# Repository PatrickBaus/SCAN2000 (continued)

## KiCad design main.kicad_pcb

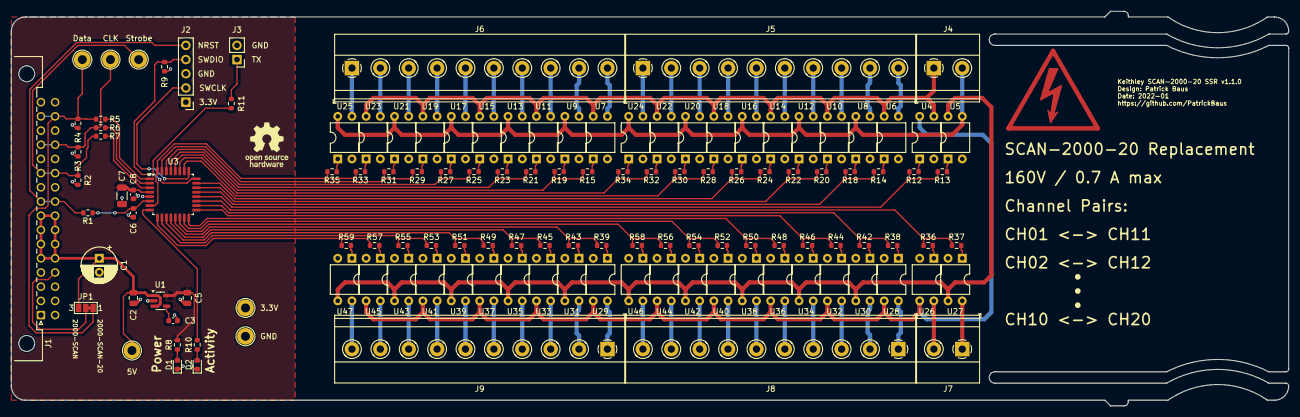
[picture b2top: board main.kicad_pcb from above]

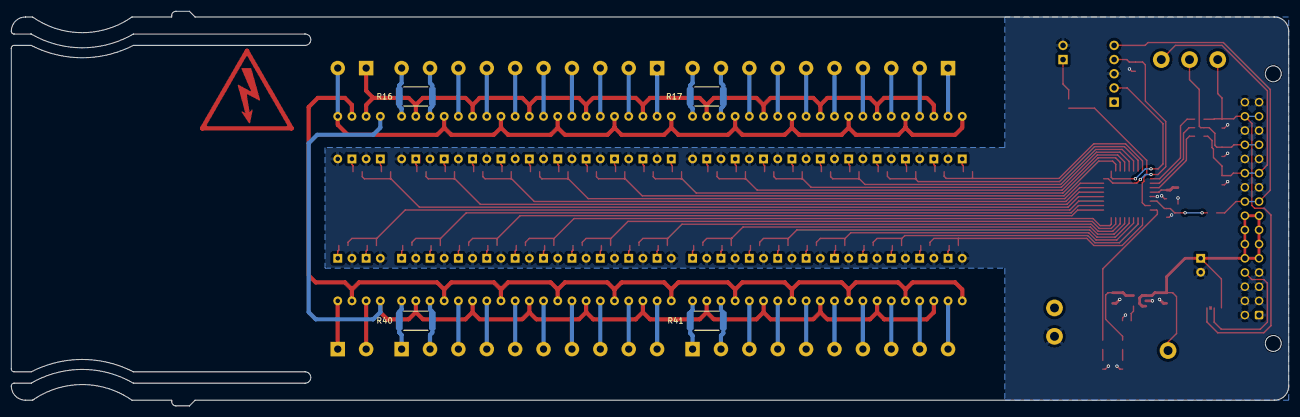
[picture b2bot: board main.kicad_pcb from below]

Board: 2 copper layers, 228.6 x 70.6 mm, 132 parts (4 on the bottom side), 132 nets.

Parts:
C1: 10u; CP_Radial_D6.3mm_P2.50mm
C2, C5: 1u; C_0805_2012Metric
C3, C6, C8: 100n; C_0603_1608Metric
C7: 4.7u; C_1206_3216Metric
D1, D2: Green; LED_0603_1608Metric
J1: Conn_02x16_Row_Letter_First; DIN41612_B2_2x16_Male_Horizontal_THT
J2: Conn_01x05; PinHeader_1x05_P2.54mm_Vertical
J3: Conn_01x02; PinHeader_1x02_P2.54mm_Vertical
J4, J7: Screw_Terminal_01x02; TerminalBlock_Phoenix_SMKDSN-1,5-2-5.08_1x02_P5.08mm_Horizo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
J5, J6, J8, J9: Screw_Terminal_01x10; TerminalBlock_Phoenix_SMKDSN-1,5-10-5.08_1x10_P5.08mm_Horiz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
JP1: SolderJumper_3_Bridged12; SolderJumper-3_P1.3mm_Bridged12_Pad1.0x1.5mm_NumberLabels
LOGO2: Logo_Open_Hardware_Small; OSHW-Logo_7.5x8mm_SilkScreen
R1, R5, R6, R7, R8, R10, R11, R12, R13, R14, R15, R18, R19, R20, R21, R22, R23, R24, R25, R26, R27, R28, R29, R30, R31, R32, R33, R34, R35, R36, R37, R38, R39, R42, R43, R44, R45, R46, R47, R48, R49, R50, R51, R52, R53, R54, R55, R56, R57, R58, R59: 330R; R_0603_1608Metric
R2, R3, R4, R9: 10k; R_0603_1608Metric
R16, R17, R40, R41: 2m; R_2512_6332Metric
SYM1: SYM_Flash_Small; Symbol_HighVoltage_Triangle_17x15mm_Copper
TP1, TP2, TP3, TP4, TP5, TP6: TestPoint; TestPoint_Loop_D2.60mm_Drill1.6mm_Beaded
U1: TPS73233DBVR; SOT-23-5
U3: STM32G070KBT6; LQFP-32_7x7mm_P0.8mm
U4, U5, U6, U7, U8, U9, U10, U11, U12, U13, U14, U15, U16, U17, U18, U19, U20, U21, U22, U23, U24, U25, U26, U27, U28, U29, U30, U31, U32, U33, U34, U35, U36, U37, U38, U39, U40, U41, U42, U43, U44, U45, U46, U47: TLP3558A; DIP-4_W7.62mm

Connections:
+3V3: C5.1, C7.1, C8.1, J2.1, R8.1, TP2.1, U1.5 (OUT), U3.4 (VDD/VDDA)
+5V: C1.1, C2.1, J1.a5, J1.a6, J1.a7, J1.a8, J1.b5, J1.b6, J1.b7, J1.b8, JP1.3 (B), TP1.1, U1.1 (IN), U1.3 (EN)
/CLK: J1.a13, J1.b13, R3.1, R6.2, TP5.1
/DATA: J1.a15, J1.b15, JP1.1 (A), R4.1, R5.2, TP4.1
/ID: J1.b4, JP1.2 (C)
/Microcontroller/Bus2_input_enable: R12.2, R13.2, U3.20 (PC6)
/Microcontroller/Bus2_sense_enable: R36.2, R37.2, U3.19 (PA9)
/Microcontroller/CH1: R14.2, R18.2, U3.21 (PA10)
/Microcontroller/CH2: R20.2, R22.2, U3.22 (PA11)
/Microcontroller/CH3: R24.2, R26.2, U3.23 (PA12)
/Microcontroller/CH4: R28.2, R30.2, U3.26 (PA15)
/Microcontroller/CH5: R32.2, R34.2, U3.27 (PB3)
/Microcontroller/CH6: R15.2, R19.2, U3.28 (PB4)
/Microcontroller/CH7: R21.2, R23.2, U3.29 (PB5)
/Microcontroller/CH8: R25.2, R27.2, U3.30 (PB6)
/Microcontroller/CH9: R29.2, R31.2, U3.31 (PB7)
/Microcontroller/CH10: R33.2, R35.2, U3.32 (PB8)
/Microcontroller/CH11: R38.2, R42.2, U3.18 (PA8)
/Microcontroller/CH12: R44.2, R46.2, U3.17 (PB2)
/Microcontroller/CH13: R48.2, R50.2, U3.16 (PB1)
/Microcontroller/CH14: R52.2, R54.2, U3.15 (PB0)
/Microcontroller/CH15: R56.2, R58.2, U3.14 (PA7)
/Microcontroller/CH16: R39.2, R43.2, U3.13 (PA6)
/Microcontroller/CH17: R45.2, R47.2, U3.12 (PA5)
/Microcontroller/CH18: R49.2, R51.2, U3.11 (PA4)
/Microcontroller/CH19: R53.2, R55.2, U3.10 (PA3)
/Microcontroller/CH20: R57.2, R59.2, U3.9 (PA2)
/Microcontroller/CLK: R6.1, U3.2 (PC14)
/Microcontroller/DATA: R5.1, U3.1 (PB9)
/Microcontroller/LED: R10.1, U3.8 (PA1)
/Microcontroller/STROBE: R7.1, U3.3 (PC15)
/Microcontroller/SWCLK: J2.2, U3.25 (PA14)
/Microcontroller/SWDIO: J2.4, R9.1, U3.24 (PA13)
/Microcontroller/TX: R11.2, U3.7 (PA0)
/Relays/Input pins/Bus_HIGH: U4.4, U26.3, U28.3, U29.3, U32.3, U33.3, U36.3, U37.3, U40.3, U41.3, U44.3, U45.3
/Relays/Input pins/Bus_LOW: U5.4, U27.3, U30.3, U31.3, U34.3, U35.3, U38.3, U39.3, U42.3, U43.3, U46.3, U47.3
/Relays/Input pins/Out_HIGH: J4.1, U4.3, U6.4, U7.4, U10.4, U11.4, U14.4, U15.4, U18.4, U19.4, U22.4, U23.4
/Relays/Input pins/Out_LOW: J4.2, U5.3, U8.4, U9.4, U12.4, U13.4, U16.4, U17.4, U20.4, U21.4, U24.4, U25.4
/Relays/Input/Sense pins/Sense_HIGH: J7.2, U26.4
/Relays/Input/Sense pins/Sense_LOW: J7.1, U27.4
/STROBE: J1.a11, J1.b11, R2.1, R7.2, TP6.1
/~NRST: J1.a9, J1.b9, J2.5, R1.2
GND: C1.2, C2.2, C3.2, C5.2, C6.2, C7.2, C8.2, D1.1 (K), D2.1 (K), J1.a1, J1.a2, J1.a3, J1.a4, J1.a10, J1.a12, J1.a14, J1.a16, J1.b1, J1.b2, J1.b3, J1.b10, J1.b12, J1.b14, J1.b16, J2.3, J3.2, R2.2, R3.2, R4.2, R9.2, TP3.1, U1.2 (GND), U3.5 (VSS/VSSA), U4.2, U5.2, U6.2, U7.2, U8.2, U9.2, U10.2, U11.2, U12.2, U13.2, U14.2, U15.2, U16.2, U17.2, U18.2, U19.2, U20.2, U21.2, U22.2, U23.2, U24.2, U25.2, U26.2, U27.2, U28.2, U29.2, U30.2, U31.2, U32.2, U33.2, U34.2, U35.2, U36.2, U37.2, U38.2, U39.2, U40.2, U41.2, U42.2, U43.2, U44.2, U45.2, U46.2, U47.2
unnamed: D1.2 (A), R8.2
unnamed: D2.2 (A), R10.2
unnamed: J3.1, R11.1
unnamed: J5.1, U24.3
unnamed: J5.2, U22.3
unnamed: J5.3, U20.3
unnamed: J5.4, U18.3
unnamed: J5.5, U16.3
unnamed: J5.6, U14.3
unnamed: J5.7, U12.3
unnamed: J5.8, U10.3
unnamed: J5.9, R16.1, U8.3
unnamed: J5.10, R16.2, U6.3
unnamed: J6.1, U25.3
unnamed: J6.2, U23.3
unnamed: J6.3, U21.3
unnamed: J6.4, U19.3
unnamed: J6.5, U17.3
unnamed: J6.6, U15.3
unnamed: J6.7, U13.3
unnamed: J6.8, U11.3
unnamed: J6.9, R17.1, U9.3
unnamed: J6.10, R17.2, U7.3
unnamed: J8.1, R40.2, U28.4
unnamed: J8.2, R40.1, U30.4
unnamed: J8.3, U32.4
unnamed: J8.4, U34.4
unnamed: J8.5, U36.4
unnamed: J8.6, U38.4
unnamed: J8.7, U40.4
unnamed: J8.8, U42.4
unnamed: J8.9, U44.4
unnamed: J8.10, U46.4
unnamed: J9.1, R41.2, U29.4
unnamed: J9.2, R41.1, U31.4
unnamed: J9.3, U33.4
unnamed: J9.4, U35.4
unnamed: J9.5, U37.4
unnamed: J9.6, U39.4
unnamed: J9.7, U41.4
unnamed: J9.8, U43.4
unnamed: J9.9, U45.4
unnamed: J9.10, U47.4
unnamed: R12.1, U4.1
unnamed: R13.1, U5.1
unnamed: R14.1, U6.1
unnamed: R15.1, U7.1
unnamed: R18.1, U8.1
unnamed: R19.1, U9.1
unnamed: R20.1, U10.1
unnamed: R21.1, U11.1
unnamed: R22.1, U12.1
unnamed: R23.1, U13.1
unnamed: R24.1, U14.1
unnamed: R25.1, U15.1
unnamed: R26.1, U16.1
unnamed: R27.1, U17.1
unnamed: R28.1, U18.1
unnamed: R29.1, U19.1
unnamed: R30.1, U20.1
unnamed: R31.1, U21.1
unnamed: R32.1, U22.1
unnamed: R33.1, U23.1
unnamed: R34.1, U24.1
unnamed: R35.1, U25.1
unnamed: R36.1, U26.1
unnamed: R37.1, U27.1
unnamed: R38.1, U28.1
unnamed: R39.1, U29.1
unnamed: R42.1, U30.1
unnamed: R43.1, U31.1
unnamed: R44.1, U32.1
unnamed: R45.1, U33.1
unnamed: R46.1, U34.1
unnamed: R47.1, U35.1
unnamed: R48.1, U36.1
unnamed: R49.1, U37.1
unnamed: R50.1, U38.1
unnamed: R51.1, U39.1
unnamed: R52.1, U40.1
unnamed: R53.1, U41.1
unnamed: R54.1, U42.1
unnamed: R55.1, U43.1
unnamed: R56.1, U44.1
unnamed: R57.1, U45.1
unnamed: R58.1, U46.1
unnamed: R59.1, U47.1
unnamed: C3.1, U1.4 (NR)
unnamed: C6.1, R1.1, U3.6 (NRST)

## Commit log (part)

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2022-01-11 Added link to the firmware
2022-01-11 Replaced Picoblade connector with standard pin header Updated libraries to KiCAD 6 format
2022-01-11 Updated PCB picture to latest version
2022-01-11 Added description to the photo
2022-01-11 Add a note, that v1.1.0 and above have a rotated MCU
2022-01-15 Updated documentation
2022-01-17 Updated silkscreen
2022-01-17 Updated BOM
2022-01-18 Updated readme with more details about supported DMMs.
2022-01-31 Added screenshots of the serial data
2022-02-20 Update README.md
    Updated supported hardware
2024-09-26 Updated to KiCad 8
    - Updated libraries
    - Updated BOM, replaced obsolete parts
2024-09-26 Updated to KiCad 8 (#1)
    - Updated libraries
    - Updated BOM, replaced obsolete parts
2024-09-26 Renamed main to SCAN2000
2024-09-26 Add CI
2024-09-26 Cleanup
2024-09-26 Add a filter for the overlapping relays
2024-09-26 Removed leading space
2024-09-26 Bump version to 1.1.1
2024-09-26 Remove the BOM as this is now generated content
2024-09-26 Reworked readme
2024-09-26 Restructuring
2024-09-26 More editing for readability
2024-09-26 Add CI script (#2)
    * Renamed main files to SCAN2000
    * Add CI
    * Bump version to 1.1.1
    * Remove the BOM as this is now generated content
    * Reworked Readme
2024-09-26 Removed gerber files
2024-09-26 Moved serial protocol logs to separate folder
2024-09-26 Updated version string
2024-09-26 Updated links to the Keithley Model 2000
2024-09-26 Updated compatibility list
2024-09-27 Update README.md
    Fixed link
2024-09-27 Updated links
2024-09-27 Updated link to firmware
2024-09-27 Updated PCB image
2024-09-27 Updated BOM properties
2024-09-27 Replaced the STM32 microcontroller with an iCE40 FPGA
2024-09-27 Bump version to 2.0.2, because of the update to KiCad 8
2024-09-27 Bump PCB version to 2.0.2
2024-09-27 Updated readme for the FPGA version
2024-09-27 More clarification
2024-09-27 Fixed typos
2024-10-01 Update README.md
    Updated supported DMMs
2024-10-01 Update README.md
    Changed K SCAN2000 to K 2000-SCAN
2024-10-11 Replace the STM32 with an iCE40 FPGA (#3)
    * Replaced the STM32 microcontroller with an iCE40 FPGA
    * Bump version to 2.0.2, because of the update to KiCad 8
    * Updated BOM properties
    * Updated PCB image
    * Updated readme for the FPGA version
    * Updated links
2024-10-11 Updated link to v1
2024-11-08 Add some information on connecting the DMM to the scanner card.
2024-11-08 Add some information on connecting the DMM to the scanner card. (#4)
2024-11-08 Update README.md
    Added missing link
2024-11-08 Update README.md
    Refactoring
2024-11-22 Moved serial protocol documentation to doc/
2024-11-22 Fixed 10-ch protocol
2024-11-22 Added subdir links
2024-11-22 Rework style
2024-11-22 Clarify root dir
2024-11-22 Fix CH1 script
2024-11-26 Added plot configs
2024-11-26 Fixed documentation link
2024-11-26 Add serial protocol doc (#5)
    * Moved serial protocol documentation to doc/
    * Added plot scripts and configs
2024-12-12 Added missing layers In1.CU and In2.Cu to the CI. This fixes #6
2024-12-12 Bump version to 2.0.3
2024-12-12 Added missing layers In1.CU and In2.Cu to the CI. (#7)
    * Added missing layers In1.CU and In2.Cu to the CI. This fixes #6.
    * Bump version to 2.0.3
2025-11-26 Bump libraries from `80d58ef` to `ba5563d`
    Bumps [libraries](https://github.com/PatrickBaus/KiCad-libraries) from `80d58ef` to `ba5563d`.
    - [Commits](https://github.com/PatrickBaus/KiCad-libraries/compare/80d58efa29fc28aa49b090516bd5b7168ac740c8...ba5563d66c23dea06d561adcb039ddac5a03efdf)
    ---
    updated-dependencies:
    - dependency-name: libraries
    dependency-version: ba5563d66c23dea06d561adcb039ddac5a03efdf
2025-11-26 Bump libraries from `80d58ef` to `ba5563d` (#8)
    Bumps [libraries](https://github.com/PatrickBaus/KiCad-libraries) from `80d58ef` to `ba5563d`.
    - [Commits](https://github.com/PatrickBaus/KiCad-libraries/compare/80d58efa29fc28aa49b090516bd5b7168ac740c8...ba5563d66c23dea06d561adcb039ddac5a03efdf)
    ---
    updated-dependencies:
    - dependency-name: libraries
    dependency-version: ba5563d66c23dea06d561adcb039ddac5a03efdf
2025-12-17 Bump libraries from `ba5563d` to `d79317d`
    Bumps [libraries](https://github.com/PatrickBaus/KiCad-libraries) from `ba5563d` to `d79317d`.
    - [Commits](https://github.com/PatrickBaus/KiCad-libraries/compare/ba5563d66c23dea06d561adcb039ddac5a03efdf...d79317d926704a58090a36fac06bfafa731a048b)
    ---
    updated-dependencies:
    - dependency-name: libraries
    dependency-version: d79317d926704a58090a36fac06bfafa731a048b
2025-12-17 Bump libraries from `ba5563d` to `d79317d` (#9)
    Bumps [libraries](https://github.com/PatrickBaus/KiCad-libraries) from `ba5563d` to `d79317d`.
    - [Commits](https://github.com/PatrickBaus/KiCad-libraries/compare/ba5563d66c23dea06d561adcb039ddac5a03efdf...d79317d926704a58090a36fac06bfafa731a048b)
    ---
    updated-dependencies:
    - dependency-name: libraries
    dependency-version: d79317d926704a58090a36fac06bfafa731a048b
2026-02-09 Bump libraries from `d79317d` to `4179135`
    Bumps [libraries](https://github.com/PatrickBaus/KiCad-libraries) from `d79317d` to `4179135`.
    - [Commits](https://github.com/PatrickBaus/KiCad-libraries/compare/d79317d926704a58090a36fac06bfafa731a048b...41791358010d2de5d2401e25bd30de257630acf6)
    ---
    updated-dependencies:
    - dependency-name: libraries
    dependency-version: 41791358010d2de5d2401e25bd30de257630acf6
2026-02-09 Bump libraries from `d79317d` to `4179135` (#10)
    Bumps [libraries](https://github.com/PatrickBaus/KiCad-libraries) from `d79317d` to `4179135`.
    - [Commits](https://github.com/PatrickBaus/KiCad-libraries/compare/d79317d926704a58090a36fac06bfafa731a048b...41791358010d2de5d2401e25bd30de257630acf6)
    ---
    updated-dependencies:
    - dependency-name: libraries
    dependency-version: 41791358010d2de5d2401e25bd30de257630acf6
2026-04-30 [gha] Bump actions/checkout from 4 to 6
    Bumps [actions/checkout](https://github.com/actions/checkout) from 4 to 6.
    - [Release notes](https://github.com/actions/checkout/releases)
    - [Changelog](https://github.com/actions/checkout/blob/main/CHANGELOG.md)
    - [Commits](https://github.com/actions/checkout/compare/v4...v6)
    ---
    updated-dependencies:
2026-04-30 [gha] Bump actions/download-artifact from 4 to 8
    Bumps [actions/download-artifact](https://github.com/actions/download-artifact) from 4 to 8.
    - [Release notes](https://github.com/actions/download-artifact/releases)
    - [Commits](https://github.com/actions/download-artifact/compare/v4...v8)
    ---
    updated-dependencies:
    - dependency-name: actions/download-artifact
2026-04-30 [gha] Bump actions/upload-artifact from 4 to 7
    Bumps [actions/upload-artifact](https://github.com/actions/upload-artifact) from 4 to 7.
    - [Release notes](https://github.com/actions/upload-artifact/releases)
    - [Commits](https://github.com/actions/upload-artifact/compare/v4...v7)
    ---
    updated-dependencies:
    - dependency-name: actions/upload-artifact
2026-04-30 [gha] Bump actions/checkout from 4 to 6 (#11)
    Bumps [actions/checkout](https://github.com/actions/checkout) from 4 to 6.
    - [Release notes](https://github.com/actions/checkout/releases)
    - [Changelog](https://github.com/actions/checkout/blob/main/CHANGELOG.md)
    - [Commits](https://github.com/actions/checkout/compare/v4...v6)
    ---
    updated-dependencies:
2026-04-30 [gha] Bump actions/upload-artifact from 4 to 7 (#13)
    Bumps [actions/upload-artifact](https://github.com/actions/upload-artifact) from 4 to 7.
    - [Release notes](https://github.com/actions/upload-artifact/releases)
    - [Commits](https://github.com/actions/upload-artifact/compare/v4...v7)
    ---
    updated-dependencies:
    - dependency-name: actions/upload-artifact
2026-04-30 [gha] Bump actions/download-artifact from 4 to 8 (#12)
    Bumps [actions/download-artifact](https://github.com/actions/download-artifact) from 4 to 8.
    - [Release notes](https://github.com/actions/download-artifact/releases)
    - [Commits](https://github.com/actions/download-artifact/compare/v4...v8)
    ---
    updated-dependencies:
    - dependency-name: actions/download-artifact
2026-06-19 [gha] Bump actions/checkout from 6 to 7
    Bumps [actions/checkout](https://github.com/actions/checkout) from 6 to 7.
    - [Release notes](https://github.com/actions/checkout/releases)
    - [Changelog](https://github.com/actions/checkout/blob/main/CHANGELOG.md)
    - [Commits](https://github.com/actions/checkout/compare/v6...v7)
    ---
    updated-dependencies:
2026-06-19 [gha] Bump actions/checkout from 6 to 7 (#14)
    Bumps [actions/checkout](https://github.com/actions/checkout) from 6 to 7.
    - [Release notes](https://github.com/actions/checkout/releases)
    - [Changelog](https://github.com/actions/checkout/blob/main/CHANGELOG.md)
    - [Commits](https://github.com/actions/checkout/compare/v6...v7)
    ---
    updated-dependencies:
